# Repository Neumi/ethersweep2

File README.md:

# ethersweep
Ethernet + UDP + Json motor controller. Based on open source soft- and hardware.
Version2 has an built in AS5600 magnetic encoder for position feedback, the option for an END-stop for homing and an E-stop -just in case.
The controller uses 8.5V to 12V from a standard XT60 connector.
All built into a small form factor that fits on the backside of a NEMA 17 stepper motor.

## What it does
Ethersweep is a simple to use ethernet connected stepper motor driver. It lets you use JSON formatted string to controll stpper motors via Ethernet. 

## How to get started:
Connect ethersweep to your network via ethernet and to a +12v power source.
Once connected it serarches for an IP address on the network using DHCP. When an IP is found, the controller shows it on the display and its ready to use.

Now you can use the Python script to control the motor.

## Using Python to controll a stepper motor:

```python
import socket
import json

IP_MOTOR = "192.168.1.185" #local motor controller IP
UDP_PORT = 1337

def drive_motor(steps, speed, direction, stepmode, motor_ip):
    json_data = json.dumps({'steps': steps, 'speed': speed, 'direction': direction, 'stepmode': stepmode})
    message = json_data.encode()
    sock = socket.socket(socket.AF_INET, socket.SOCK_DGRAM)
    sock.sendto(message, (motor_ip, UDP_PORT))

drive_motor(100, 9500, 1, 32, IP_MOTOR)
```

## Video:

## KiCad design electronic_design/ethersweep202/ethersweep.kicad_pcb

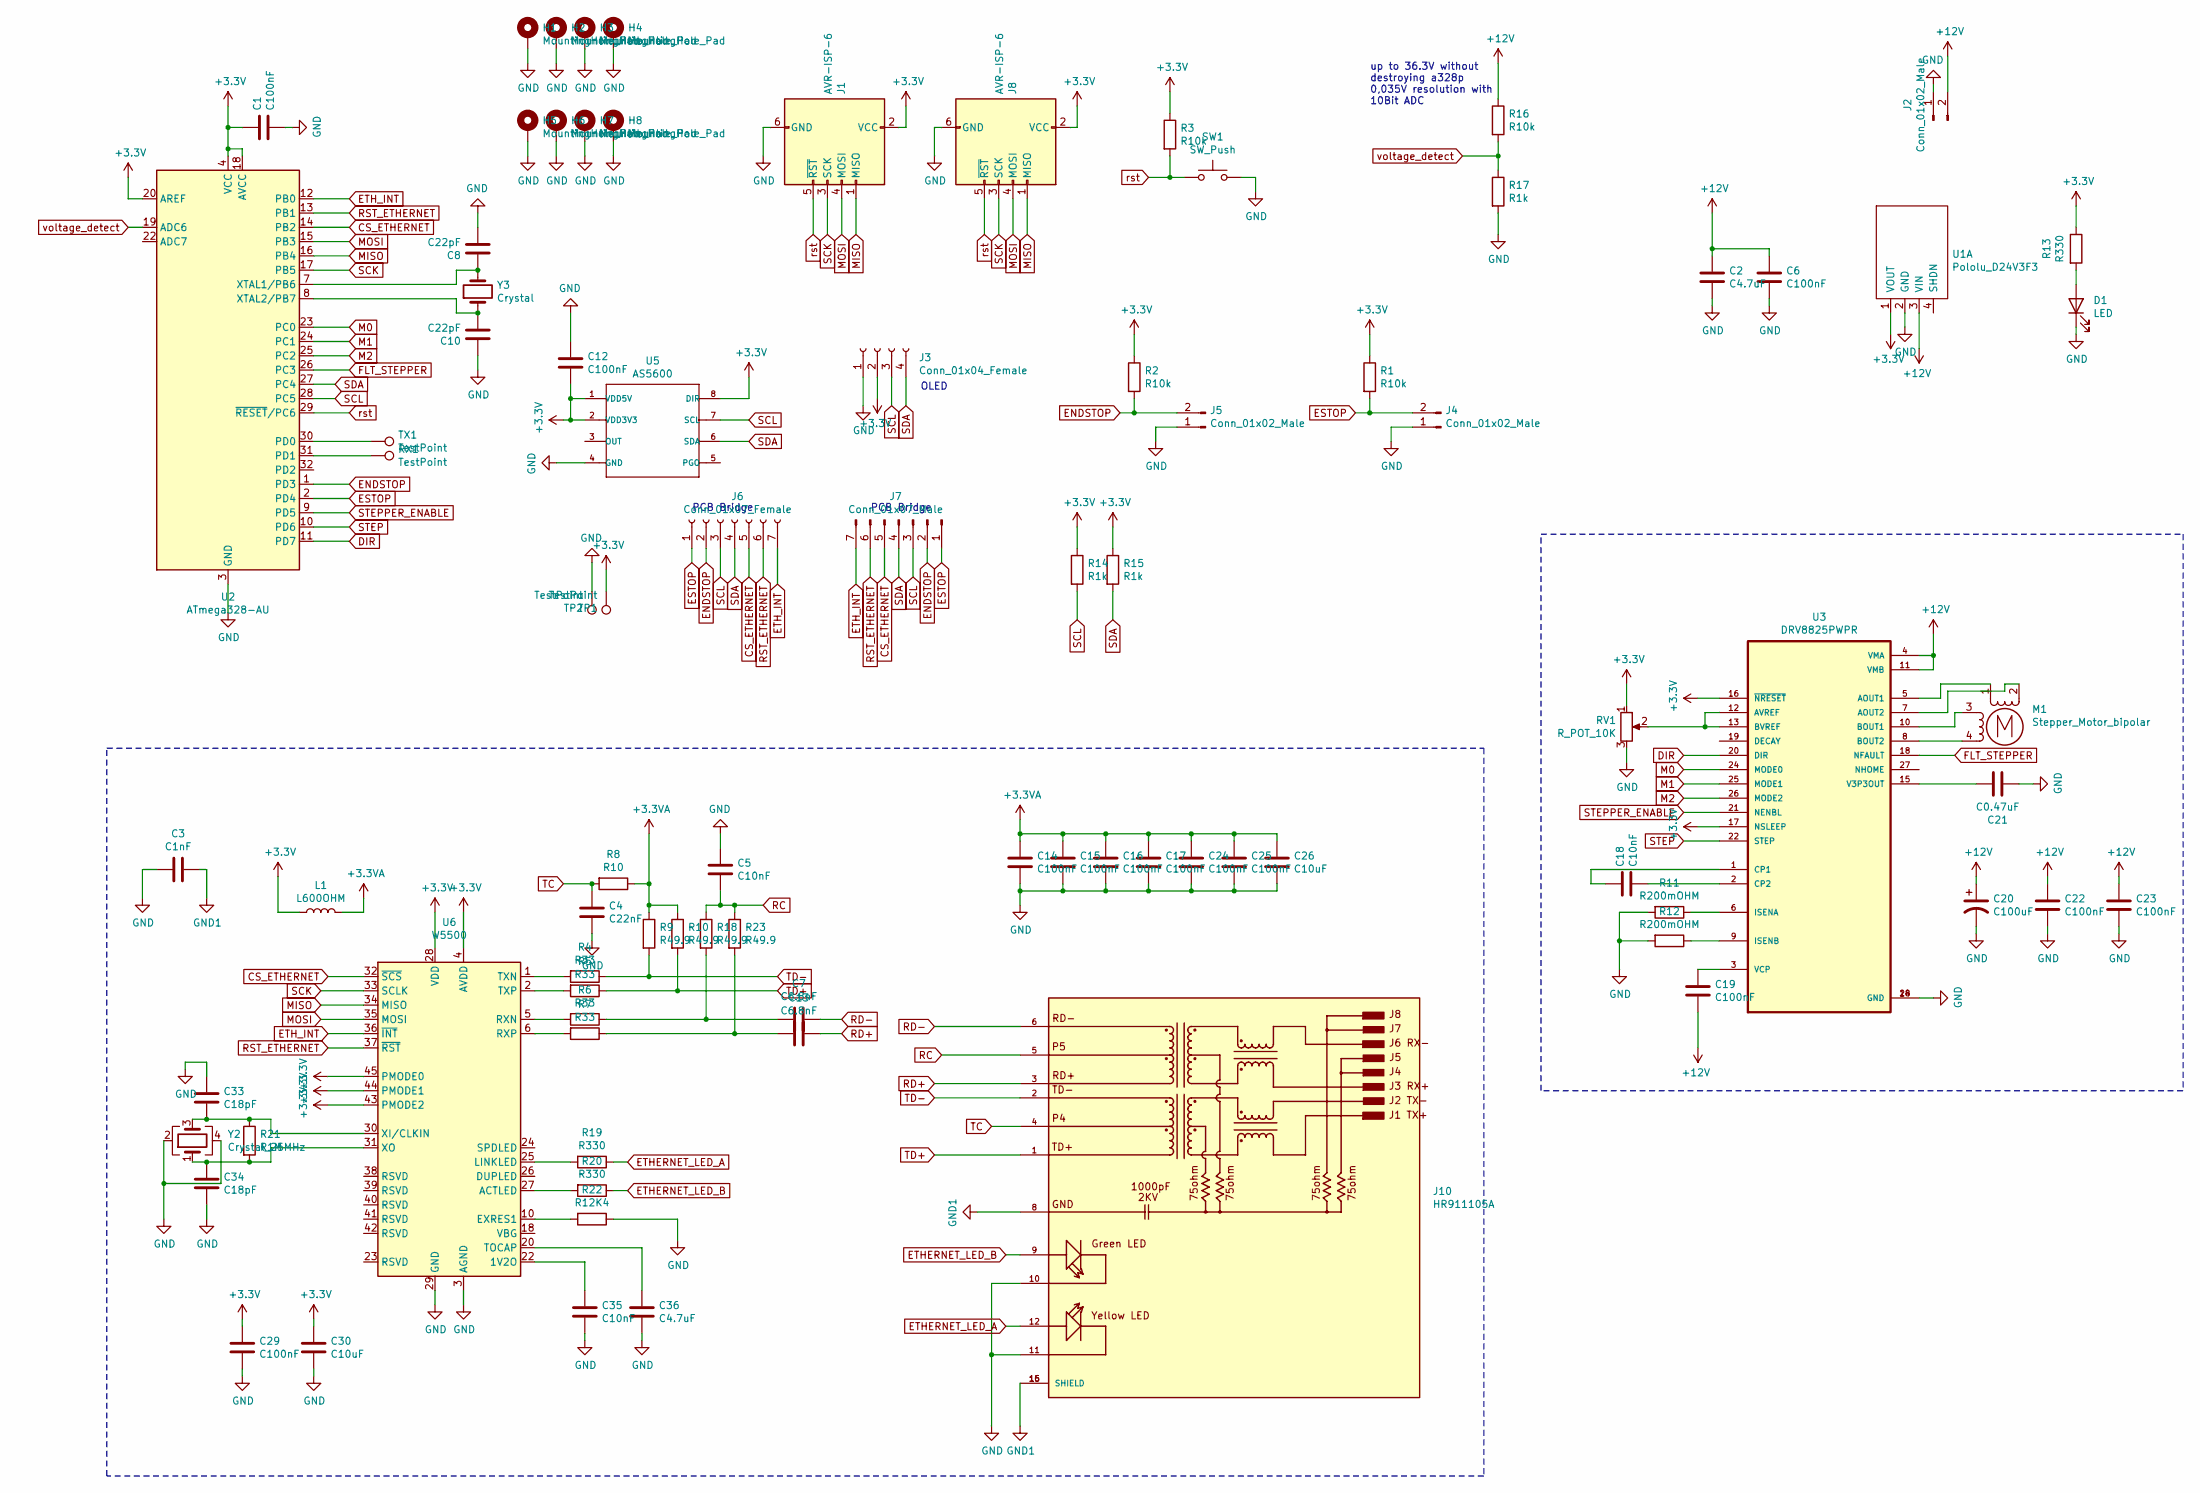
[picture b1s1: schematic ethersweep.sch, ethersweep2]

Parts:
C1, C6, C12, C19, C22, C23: C100nF; C_0805_2012Metric; LCSC C49678
C2: C4.7uF; C_1206_3216Metric; LCSC C29823
C3: C1nF; R_1206_3216Metric; LCSC C35216
C4: C22nF; R_0603_1608Metric; LCSC C21122
C5, C35: C10nF; C_0603_1608Metric; LCSC C57112
C7, C13: C6.8nF; R_0402_1005Metric; LCSC C1542
C8, C10: C22pF; C_0402_1005Metric; LCSC C1555
C14, C15, C16, C17, C24, C25, C29: C100nF; C_0402_1005Metric; LCSC C1525
C18: C10nF; C_0805_2012Metric; LCSC C1710
C20: C100uF; CP_Elec_8x10; LCSC C176665
C21: C0.47uF; C_0805_2012Metric; LCSC C13967
C26, C30: C10uF; C_0805_2012Metric; LCSC C15850
C33, C34: C18pF; C_0402_1005Metric; LCSC C1549
C36: C4.7uF; C_0402_1005Metric; LCSC C23733
D1: LED; LED_0805_2012Metric; LCSC C84256
H1, H2, H3, H4, H5, H6, H7, H8: MountingHole_Pad; MountingHole_3.2mm_M3_Pad_Via
J1, J8: AVR-ISP-6; IDC-Header_2x03_P2.54mm_Vertical
J2: Conn_01x02_Male; AMASS_XT30PW-M_1x02_P2.50mm_Horizontal
J3: Conn_01x04_Female; PinHeader_1x04_P2.54mm_Vertical
J4, J5: Conn_01x02_Male; JST_EH_S2B-EH_1x02_P2.50mm_Horizontal
J6: Conn_01x07_Female; PinHeader_1x07_P2.54mm_Vertical
J7: Conn_01x07_Male; PinHeader_1x07_P2.54mm_Vertical
J10: HR911105A; HANRUN_HR911105A; PARTREV A; LCSC C12074
L1: L600OHM; L_0805_2012Metric; LCSC C1017
M1: Stepper_Motor_bipolar; PinHeader_2x02_P2.54mm_Vertical_SMD
R1, R2, R3: R10k; R_0603_1608Metric; LCSC C25804
R4, R5, R6, R7: R33; R_0805_2012Metric; LCSC C17634
R8: R10; R_0805_2012Metric; LCSC C17415
R9, R10, R18, R23: R49.9; R_0603_1608Metric; LCSC C23185
R11, R12: R200mOHM; R_1206_3216Metric; LCSC C25335
R13, R19, R20: R330; R_0603_1608Metric; LCSC C23138
R14, R15: R1k; R_0603_1608Metric; LCSC C21190
R16: R10k; R_0603_1608Metric
R17: R1k; R_0603_1608Metric
R21: R1M; R_0805_2012Metric; LCSC C17514
R22: R12K4; R_0805_2012Metric; LCSC C30908
RV1: R_POT_10K; Potentiometer_Bourns_3296W_Vertical; LCSC C118954
RX1: TestPoint; TestPoint_Pad_D2.0mm
SW1: SW_Push; SW_Push_SPST_NO_Alps_SKRK
TP1, TP2: TestPoint; TestPoint_Pad_D2.0mm
TX1: TestPoint; TestPoint_Pad_D2.0mm
U1: Pololu_D24V3F3
U2: ATmega328-AU; TQFP-32_7x7mm_P0.8mm; LCSC C14877
U3: DRV8825PWPR; IC_TPS61196PWPRQ1; LCSC C81582
U5: AS5600
U6: W5500; LQFP-48_7x7mm_P0.5mm
Y2: Crystal_25MHz; Crystal_SMD_3225-4Pin_3.2x2.5mm; LCSC C9006
Y3: Crystal; Crystal_SMD_5032-2Pin_5.0x3.2mm; LCSC C115962

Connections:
+12V: C2.1, C6.1, C19.2, C20.1, C22.1, C23.1, J2.2, R16.1, U1.3 (VIN), U3.4 (VMA), U3.11 (VMB)
CS_ETHERNET: J6.5, J7.5, U2.14 (PB2), U6.32 (~SCS)
DIR: U2.11 (PD7), U3.20 (DIR)
ENDSTOP: J5.2, J6.2, J7.2, R2.2, U2.1 (PD3)
ESTOP: J4.2, J6.1, J7.1, R1.2, U2.2 (PD4)
ETHERNET_LED_A: J10.12, R19.1
ETHERNET_LED_B: J10.9, R20.1
ETH_INT: J6.7, J7.7, U2.12 (PB0), U6.36 (~INT)
FLT_STEPPER: U2.26 (PC3), U3.18 (NFAULT)
GND: C1.2, C2.2, C3.2, C4.1, C5.1, C6.2, C8.2, C10.1, C12.1, C14.2, C15.2, C16.2, C17.2, C20.2, C21.2, C22.2, C23.2, C24.2, C25.2, C26.2, C29.2, C30.2, C33.1, C34.2, C35.2, C36.2, D1.1 (K), H1.1, H2.1, H3.1, H4.1, H5.1, H6.1, H7.1, H8.1, J1.6 (GND), J2.1, J3.1, J4.1, J5.1, J8.6 (GND), J10.10, J10.11, R11.2, R12.2, R17.2, R22.1, RV1.3, SW1.2, TP2.1, U1.2 (GND), U2.3 (GND), U2.5 (GND), U2.21 (GND), U3.14 (GND), U3.28 (GND), U5.4 (GND), U6.3 (AGND), U6.9 (AGND), U6.14 (AGND), U6.16 (AGND), U6.19 (AGND), U6.29 (GND), U6.48 (AGND), Y2.2, Y2.4; also elsewhere on the board
GND1: C3.1, J10.8, J10.15 (SHIELD), J10.16 (SHIELD)
M0: U2.23 (PC0), U3.24 (MODE0)
M1: U2.24 (PC1), U3.25 (MODE1)
M2: U2.25 (PC2), U3.26 (MODE2)
MISO: J1.1 (MISO), J8.1 (MISO), U2.16 (PB4), U6.34 (MISO)
MOSI: J1.4 (MOSI), J8.4 (MOSI), U2.15 (PB3), U6.35 (MOSI)
unnamed: C7.2, R6.1, R18.2
unnamed: C8.1, U2.7 (XTAL1/PB6), Y3.2
unnamed: C10.2, U2.8 (XTAL2/PB7), Y3.1
unnamed: C13.2, R7.1, R23.2
unnamed: C18.1, U3.1 (CP1)
unnamed: C18.2, U3.2 (CP2)
unnamed: C19.1, U3.3 (VCP)
unnamed: C21.1, U3.15 (V3P3OUT)
unnamed: C33.2, R21.1, U6.30 (XI/CLKIN), Y2.3
unnamed: C34.1, R21.2, U6.31 (XO), Y2.1
unnamed: C35.1, U6.22 (1V2O)
unnamed: C36.1, U6.20 (TOCAP)
unnamed: D1.2 (A), R13.2
unnamed: M1.1, U3.5 (AOUT1)
unnamed: M1.2 (-), U3.7 (AOUT2)
unnamed: M1.3, U3.10 (BOUT1)
unnamed: M1.4, U3.8 (BOUT2)
unnamed: R4.2, U6.1 (TXN)
unnamed: R5.2, U6.2 (TXP)
unnamed: R6.2, U6.5 (RXN)
unnamed: R7.2, U6.6 (RXP)
unnamed: R11.1, U3.6 (ISENA)
unnamed: R12.1, U3.9 (ISENB)
unnamed: R19.2, U6.25 (LINKLED)
unnamed: R20.2, U6.27 (ACTLED)
unnamed: R22.2, U6.10 (EXRES1)
unnamed 43: U2.32 (PD2); also elsewhere on the board
unnamed: RV1.2, U3.12 (AVREF), U3.13 (BVREF)
unnamed: RX1.1, U2.31 (PD1)
unnamed: TX1.1, U2.30 (PD0)
RC: C5.2, J10.5, R18.1, R23.1
RD+: C13.1, J10.3
RD-: C7.1, J10.6
RST_ETHERNET: J6.6, J7.6, U2.13 (PB1), U6.37 (~RST)
SCK: J1.3 (SCK), J8.3 (SCK), U2.17 (PB5), U6.33 (SCLK)
SCL: J3.3, J6.3, J7.3, R14.2, U2.28 (PC5), U5.7 (SCL)
SDA: J3.4, J6.4, J7.4, R15.2, U2.27 (PC4), U5.6 (SDA)
STEP: U2.10 (PD6), U3.22 (STEP)
STEPPER_ENABLE: U2.9 (PD5), U3.21 (NENBL)
TC: C4.2, J10.4, R8.2
TD+: J10.1, R5.1, R10.2
TD-: J10.2, R4.1, R9.2
rst: J1.5 (~RST), J8.5 (~RST), R3.2, SW1.1, U2.29 (~RESET~/PC6)
voltage_detect: R16.2, R17.1, U2.19 (ADC6)

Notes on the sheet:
up to 36.3V without destroying a328p 0,035V resolution with 10Bit ADC
OLED
PCB Bridge

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
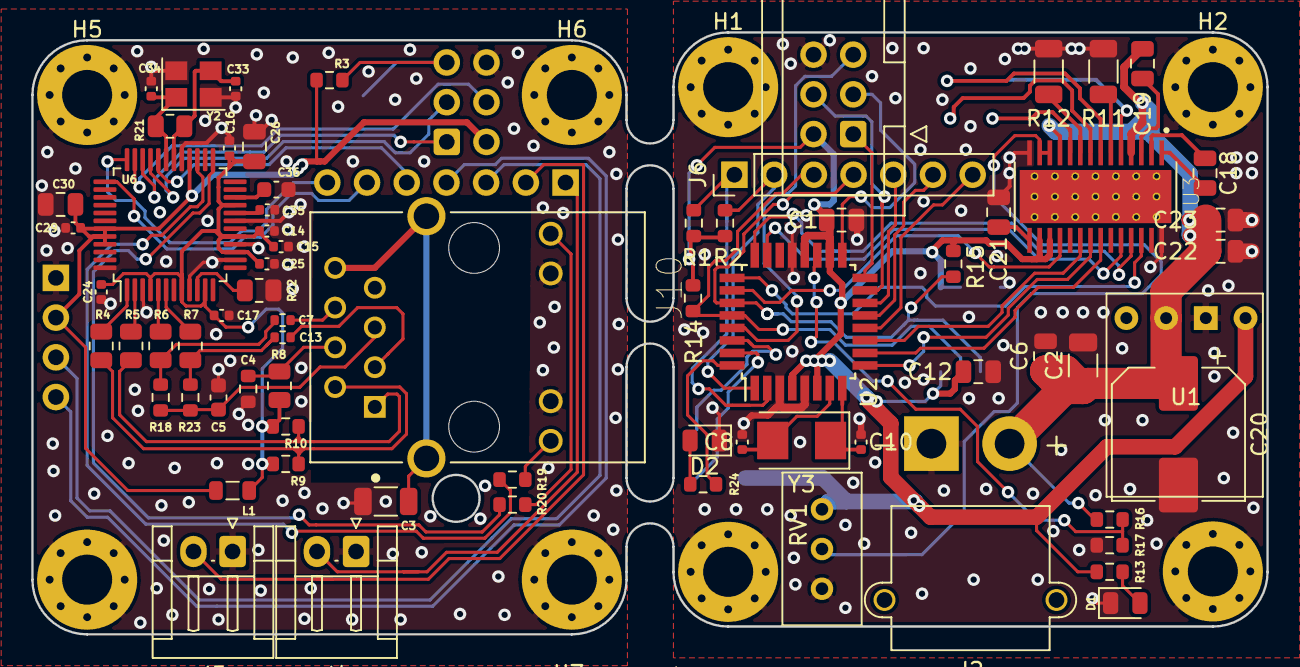
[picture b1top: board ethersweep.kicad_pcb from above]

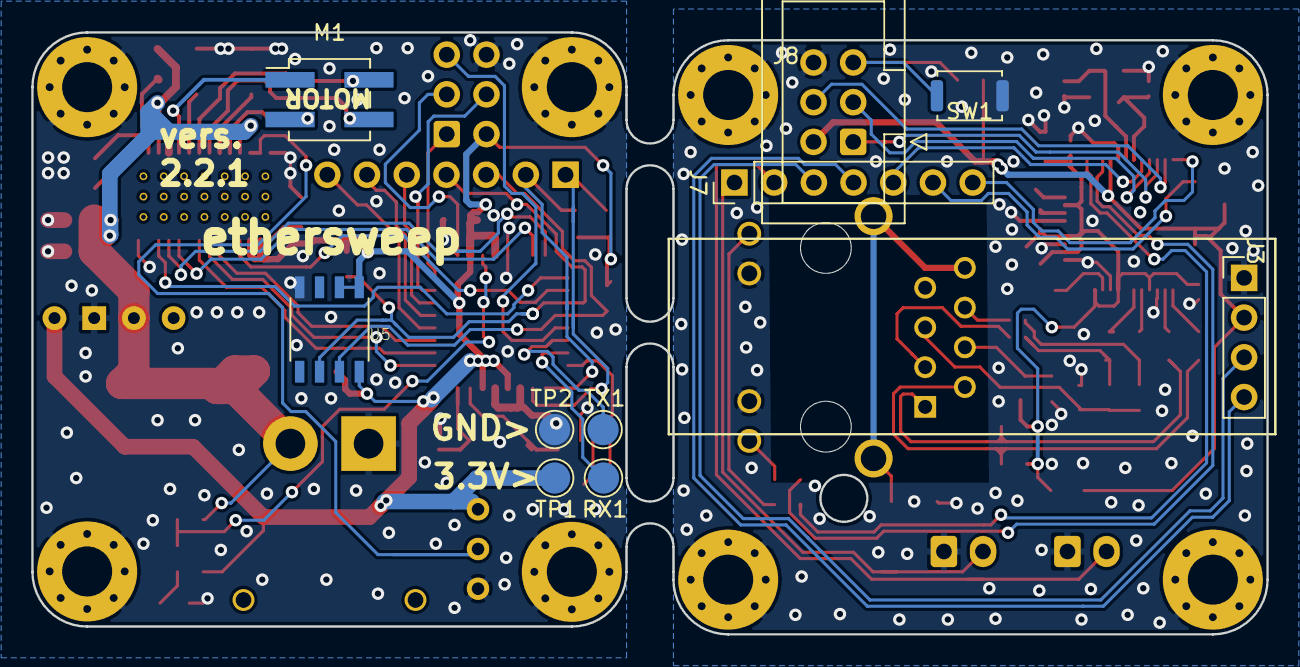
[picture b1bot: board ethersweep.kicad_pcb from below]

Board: 2 copper layers, 79.0 x 38.5 mm, 88 parts (10 on the bottom side), 63 nets.

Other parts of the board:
D2: LED; LED_0805_2012Metric
R24: R330; R_0603_1608Metric

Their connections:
GND: D2.1; also elsewhere on the board
unnamed: D2.2, R24.2
unnamed 43: R24.1; also elsewhere on the board

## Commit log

2021-02-01 added new 2.0 design files
2021-02-01 raw component layout done
2021-02-01 board layout and routing for 1st board done
2021-02-01 board layouts done
2021-02-03 board layout changed for single-piece manufacturing
2021-02-03 small via fix
2021-02-03 added images
2021-02-03 added images to md
2021-02-03 added animation
2021-02-04 design improvements and error fixes
2021-02-04 typo and info fix
2021-02-04 test
2021-02-04 test123
2021-02-04 tesdf
2021-02-04 test end
2021-02-05 changed images
2021-02-05 changed image
2021-02-08 added prod files
2021-02-09 changed resistor footprints from 805 to 603
2021-02-10 small routing changes
2021-02-10 added LCSC part numbers and changed some components for cheap manufacturing
2021-02-10 footprint changes, LCSC parts assigned, design changes
2021-02-10 design cleanup
2021-02-10 cleanup
2021-02-10 added production files, BOM and POS files with JLCPCB part numbers and orientations
2021-02-11 minor changes
2021-02-16 added hirachical sheets, changed page footers
2021-02-18 added new display layout for ethersweep2
2021-02-19 started cersion 2.0.2 with voltage detect
2021-02-19 added 2
2021-02-22 minor v202 changes
2021-02-25 reversed xt60 polarity
2021-02-25 added photo
2021-02-26 minor design changes and fixes
2021-03-03 schematic changes
2021-03-03 layout refresh
2021-03-05 202 design changed to w5500 ethernet driver
2021-03-05 added interrupt pin to w5500
2021-03-05 layout implementation board 1 done, board 2 in progress
2021-03-07 e-design changes
2021-03-07 added stl files
2021-03-10 design and layout changes
2021-03-11 new case and top files
2021-03-11 added full assembly STL
2021-03-11 shrinked file
2021-03-11 added boards
2021-03-11 added screws
2021-03-24 major power supply canges
2021-03-26 layout changes, added status led ...
2021-03-29 layout changes
2021-03-30 layout done. EMI improvements
